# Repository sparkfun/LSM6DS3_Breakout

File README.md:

SparkFun <PRODUCT NAME>
========================================

[*LSM6DS3 Breakout (SEN-13339)*](https://www.sparkfun.com/products/13339)

The LSM6DS3 Breakout board allows easy connection to the LSM6DS3.

The LSM6DS3 is a accelerometer, gyroscope, and temperature sensor with embedded functions targeted at cellphones.  It can do high sample rates and includes an 8kB FIFO buffer for burst reads.

Repository Contents
-------------------

* **/Documentation** - Data sheets, additional product information
* **/Hardware** - Eagle design files (.brd, .sch)
* **/Libraries** - Libraries for use with the LSM6DS3 Breakout
* **/Production** - Production panel files (.brd)

Documentation
--------------
* **[Library](https://github.com/sparkfun/SparkFun_LSM6DS3_Arduino_Library)** - C++ library for the LSM6DS3 Breakout.
* **[Hookup Guide](https://learn.sparkfun.com/tutorials/lsm6ds3-breakout-hookup-guide)** - Basic hookup guide for the LSM6DS3 Breakout.

Product Versions
----------------
* [SEN-13339](https://www.sparkfun.com/products/13339)- LSM6DS3 Breakout board

Version History
---------------
* [V_1.0.0](https://github.com/sparkfun/LSM6DS3_Breakout/releases/tag/V_1.0.0) - Initial product release repository
* [V_0.3.0](https://github.com/sparkfun/LSM6DS3_Breakout/releases/tag/V_0.3.0) - HW version 0.3 release

License Information
-------------------

This product is _**open source**_! 

Please review the LICENSE.md file for license information. 

If you have any questions or concerns on licensing, please contact techsupport@sparkfun.com.

Distributed as-is; no warranty is given.

- Your friends at SparkFun.

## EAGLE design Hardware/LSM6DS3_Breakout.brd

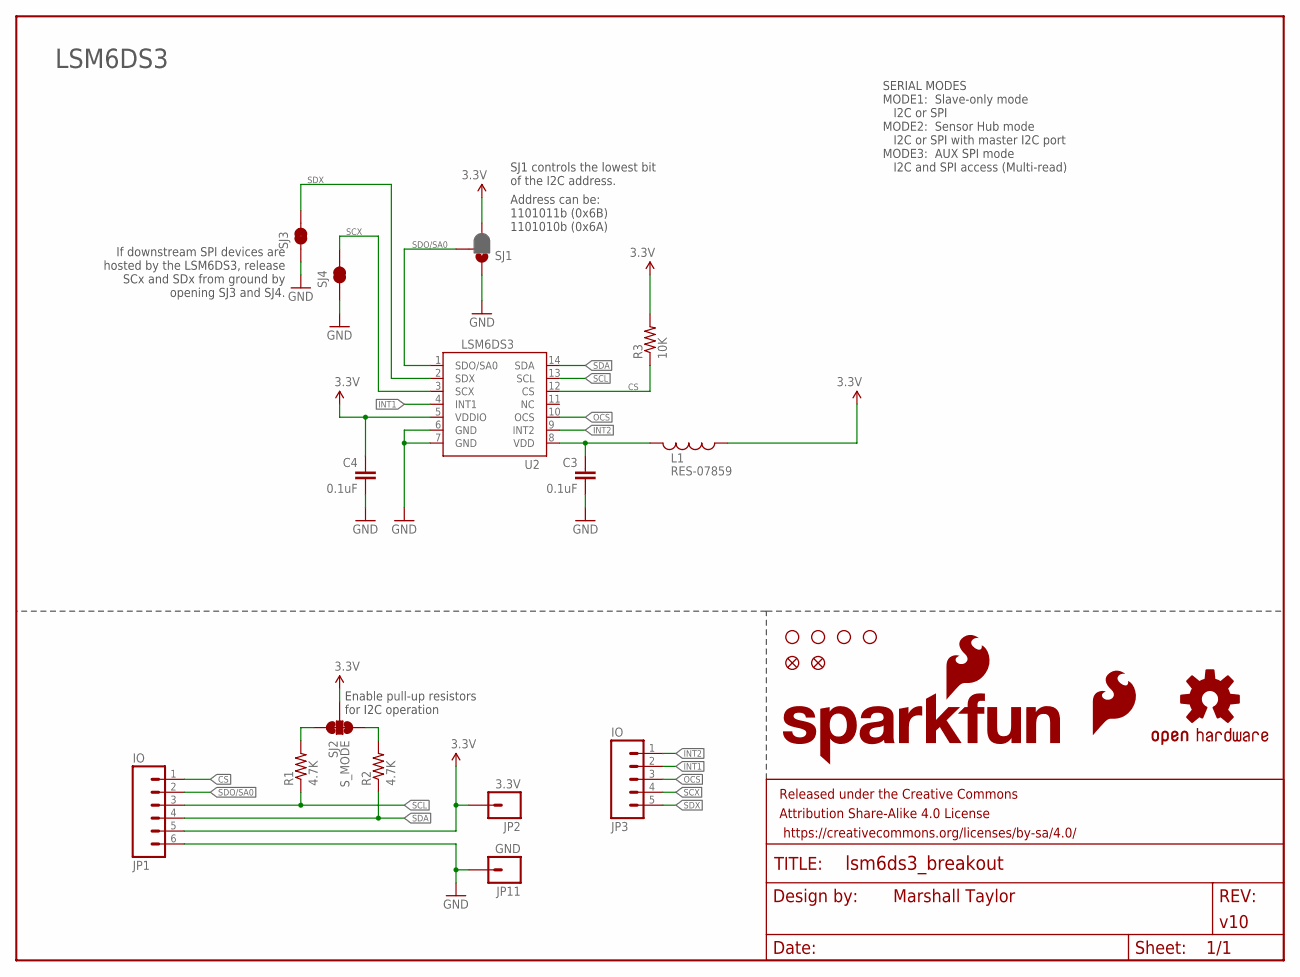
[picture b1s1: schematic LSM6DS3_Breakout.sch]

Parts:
C3, C4: 0.1uF; 0603-CAP
FID1, FID2: FIDUCIAL1X2; FIDUCIAL-1X2
FRAME1: FRAME-LETTER; CREATIVE_COMMONS
JP1: IO; 1X06_NO_SILK_YES_STOP
JP2: 3.3V; 1X01_NO_SILK
JP3: IO; 1X05
JP11: GND; 1X01_NO_SILK
L1: RES-07859; 0603
LOGO1: SFE_LOGO_FLAME.2_INCH; SFE_LOGO_FLAME_.2
LOGO2: OSHW-LOGOS; OSHW-LOGO-S
LOGO3: SFE_LOGO_NAME_FLAME.1_INCH; SFE_LOGO_NAME_FLAME_.1
R1, R2: 4.7K; 0603-RES
R3: 10K; 0603-RES
SJ1: JUMPER-PAD-3-2OF3_NC_BY_PASTE; PAD-JUMPER-3-2OF3_NC_BY_PASTE_YES_SILK_FULL_BOX
SJ2: S_MODE; PAD-JUMPER-3-3OF3_NC_BY_TRACE_YES_SILK_FULL_BOX
SJ3, SJ4: JUMPER-PAD-2-NC_BY_TRACE; PAD-JUMPER-2-NC_BY_TRACE_YES_SILK
STANDOFF1, STANDOFF2, STANDOFF3, STANDOFF4: STAND-OFF
U2: LSM6DS3; LGA14L_DOT_INDICATOR

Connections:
3.3V: C4.1, JP1.5, JP2.1, L1.1, R3.2, SJ1.3, SJ2.2, U2.5 (VDDIO)
CS: JP1.1, R3.1, U2.12 (CS)
GND: C3.2, C4.2, JP1.6, JP11.1, SJ1.1, SJ3.1, SJ4.1, U2.6 (GND), U2.7 (GND)
INT1: JP3.2, U2.4 (INT1)
INT2: JP3.1, U2.9 (INT2)
unnamed: R1.2, SJ2.1
unnamed: R2.2, SJ2.3
OCS: JP3.3, U2.10 (OCS)
SCL: JP1.3, R1.1, U2.13 (SCL)
SCX: JP3.4, SJ4.2, U2.3 (SCX)
SDA: JP1.4, R2.1, U2.14 (SDA)
SDO/SA0: JP1.2, SJ1.2, U2.1 (SDO/SA0)
SDX: JP3.5, SJ3.2, U2.2 (SDX)
VDD: C3.1, L1.2, U2.8 (VDD)

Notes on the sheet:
SJ1 controls the lowest bit of the I2C address.
LSM6DS3
If downstream SPI devices are hosted by the LSM6DS3, release SCx and SDx from ground by opening SJ3 and SJ4.
Address can be: 1101011b (0x6B) 1101010b (0x6A)
Enable pull-up resistors for I2C operation
SERIAL MODES MODE1: Slave-only mode I2C or SPI MODE2: Sensor Hub mode I2C or SPI with master I2C port MODE3: AUX SPI mode I2C and SPI access (Multi-read)

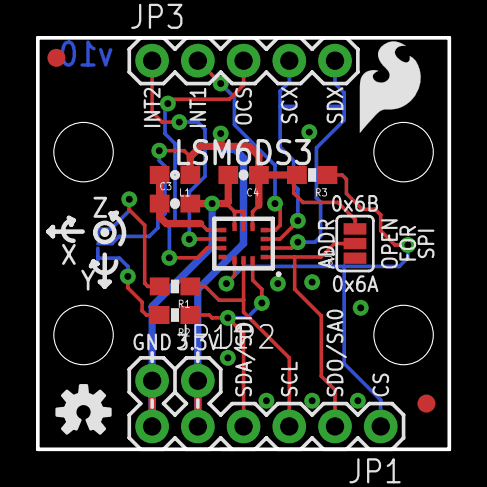
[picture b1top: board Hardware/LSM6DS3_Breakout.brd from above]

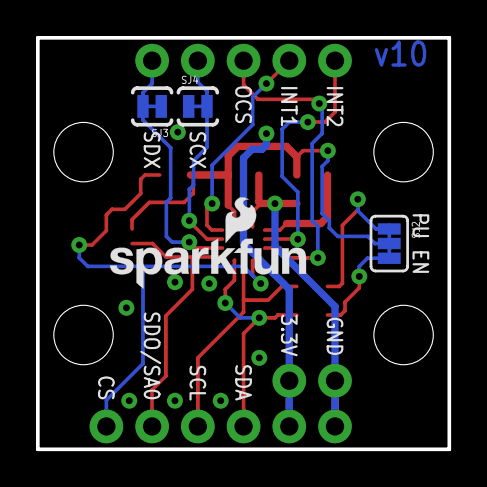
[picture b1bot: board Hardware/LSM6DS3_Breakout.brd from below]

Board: 2 copper layers, 22.9 x 22.9 mm, 25 parts (4 on the bottom side), 14 nets.

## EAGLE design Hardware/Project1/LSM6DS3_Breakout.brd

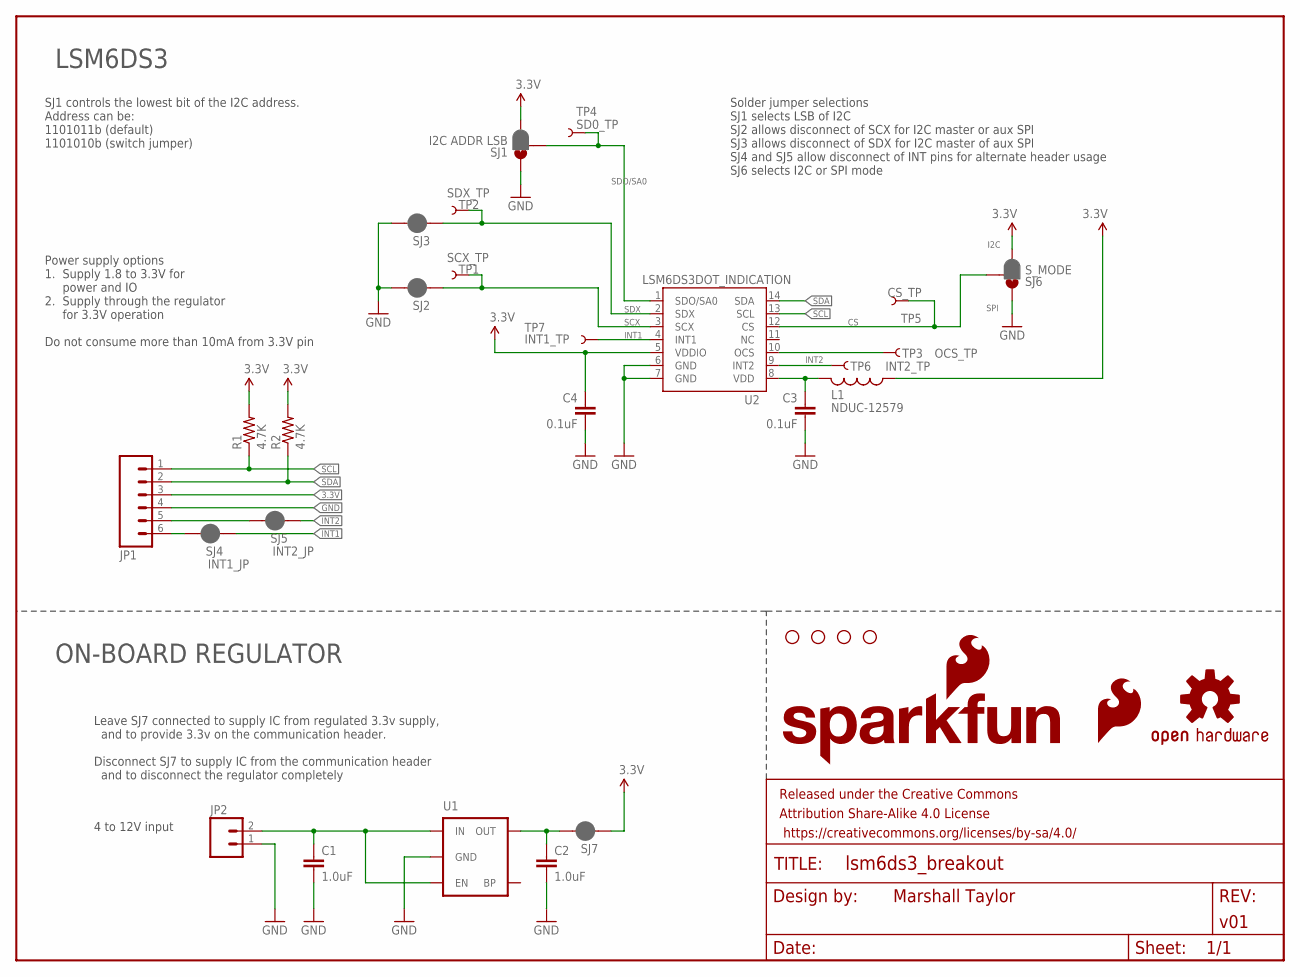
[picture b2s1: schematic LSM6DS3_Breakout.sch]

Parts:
C1, C2: 1.0uF; 0603-CAP
C3, C4: 0.1uF; 0603-CAP
FRAME1: FRAME-LETTER; CREATIVE_COMMONS
JP1: M06SILK_FEMALE_PTH; 1X06
JP2: M02PTH; 1X02
L1: NDUC-12579; 0603
LOGO1: SFE_LOGO_NAME_FLAME.1_INCH; SFE_LOGO_NAME_FLAME_.1
LOGO2: OSHW-LOGOS; OSHW-LOGO-S
LOGO3: SFE_LOGO_FLAME.4_INCH; SFE_LOGO_FLAME_.4
R1, R2: 4.7K; 0603-RES
SJ1: I2C ADDR LSB; PAD-JUMPER-3-2OF3_NC_BY_PASTE_YES_SILK_FULL_BOX
SJ2, SJ3, SJ7: JUMPER-PAD-2-NC_BY_PASTE; PAD-JUMPER-2-NC_BY_PASTE_YES_SILK
SJ4: INT1_JP; PAD-JUMPER-2-NC_BY_PASTE_YES_SILK
SJ5: INT2_JP; PAD-JUMPER-2-NC_BY_PASTE_YES_SILK
SJ6: S_MODE; PAD-JUMPER-3-2OF3_NC_BY_PASTE_YES_SILK_FULL_BOX
STANDOFF1, STANDOFF2, STANDOFF3, STANDOFF4: STAND-OFF
TP1: SCX_TP; TP_15TH
TP2: SDX_TP; TP_15TH
TP3: OCS_TP; TP_15TH
TP4: SD0_TP; TP_15TH
TP5: CS_TP; TP_15TH
TP6: INT2_TP; TP_15TH
TP7: INT1_TP; TP_15TH
U1: MIC52053.3V; SOT23-5
U2: LSM6DS3DOT_INDICATION; LGA14L_DOT_INDICATOR

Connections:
3.3V: C4.1, JP1.3, L1.1, R1.2, R2.2, SJ1.3, SJ6.3, SJ7.1, U2.5 (VDDIO)
CS: SJ6.2, TP5.P$1, U2.12 (CS)
GND: C1.2, C2.2, C3.2, C4.2, JP1.4, JP2.1, SJ1.1, SJ2.2, SJ3.2, SJ6.1, U1.2 (GND), U2.6 (GND), U2.7 (GND)
INT1: SJ4.1, TP7.P$1, U2.4 (INT1)
INT2: SJ5.1, TP6.P$1, U2.9 (INT2)
unnamed: C3.1, L1.2, U2.8 (VDD)
unnamed: TP3.P$1, U2.10 (OCS)
unnamed: JP1.5, SJ5.2
unnamed: JP1.6, SJ4.2
unnamed: C1.1, JP2.2, U1.1 (IN), U1.3 (EN)
unnamed: C2.1, SJ7.2, U1.5 (OUT)
SCL: JP1.1, R1.1, U2.13 (SCL)
SCX: SJ2.1, TP1.P$1, U2.3 (SCX)
SDA: JP1.2, R2.1, U2.14 (SDA)
SDO/SA0: SJ1.2, TP4.P$1, U2.1 (SDO/SA0)
SDX: SJ3.1, TP2.P$1, U2.2 (SDX)

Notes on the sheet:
SPI
I2C
SJ1 controls the lowest bit of the I2C address. Address can be: 1101011b (default) 1101010b (switch jumper)
Leave SJ7 connected to supply IC from regulated 3.3v supply, and to provide 3.3v on the communication header. Disconnect SJ7 to supply IC from the communication header and to disconnect the regulator completely
4 to 12V input
Do not consume more than 10mA from 3.3V pin
Power supply options 1. Supply 1.8 to 3.3V for power and IO 2. Supply through the regulator for 3.3V operation
ON-BOARD REGULATOR
LSM6DS3
Solder jumper selections SJ1 selects LSB of I2C SJ2 allows disconnect of SCX for I2C master or aux SPI SJ3 allows disconnect of SDX for I2C master of aux SPI SJ4 and SJ5 allow disconnect of INT pins for alternate header usage SJ6 selects I2C or SPI mode

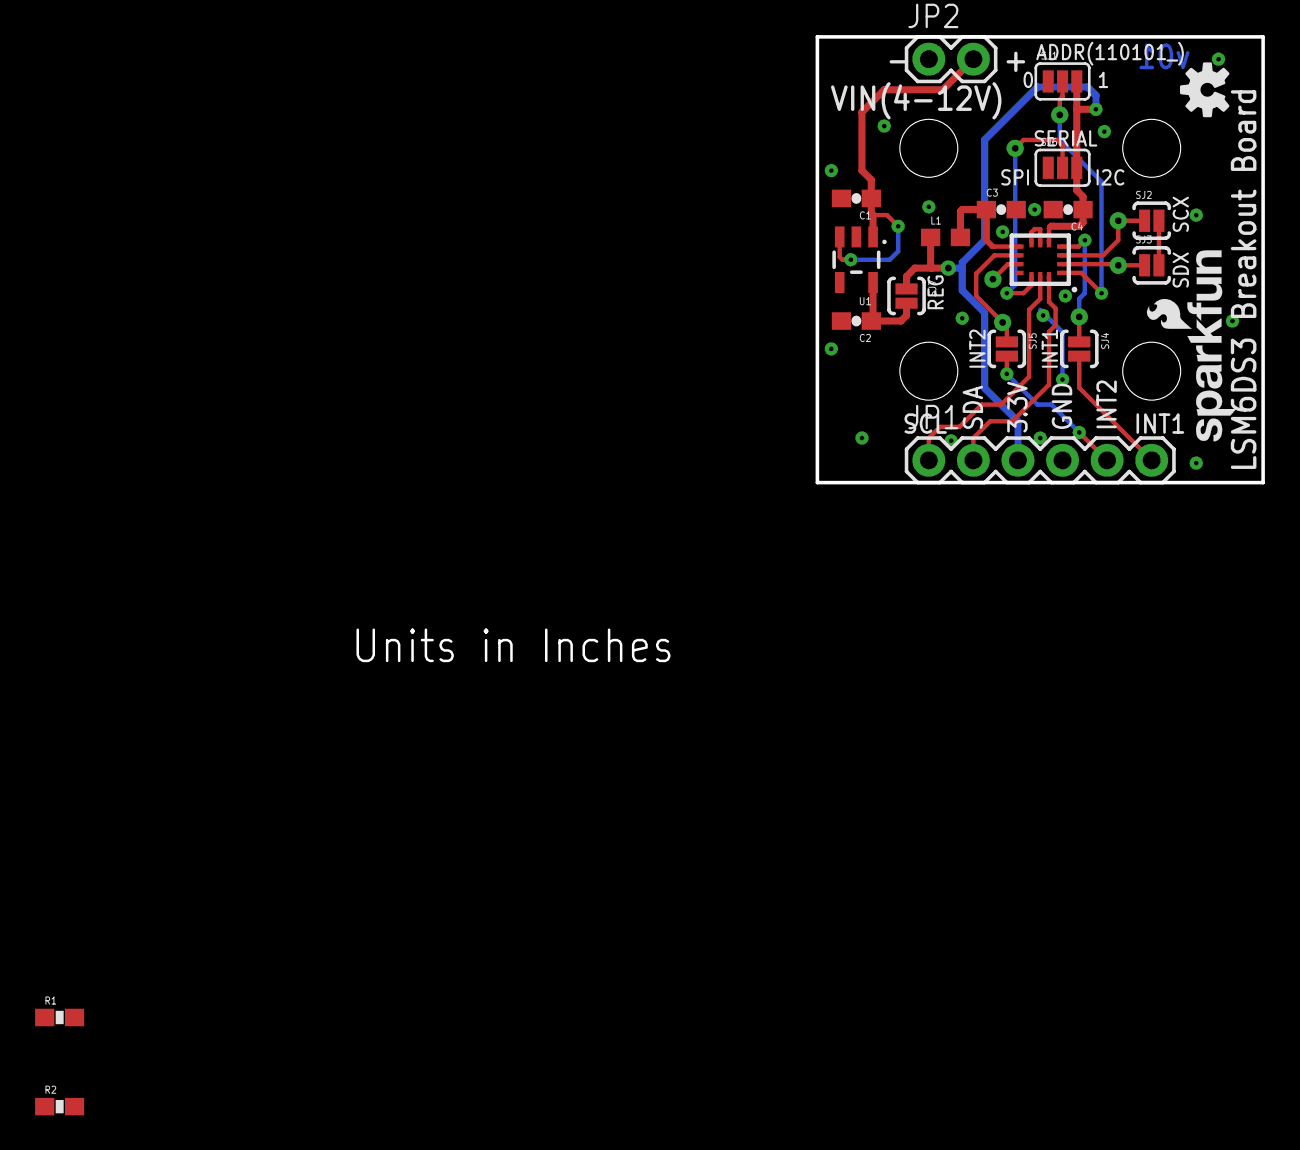
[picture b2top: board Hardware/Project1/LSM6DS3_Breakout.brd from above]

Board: 2 copper layers, 25.4 x 25.4 mm, 33 parts (1 on the bottom side), 16 nets.

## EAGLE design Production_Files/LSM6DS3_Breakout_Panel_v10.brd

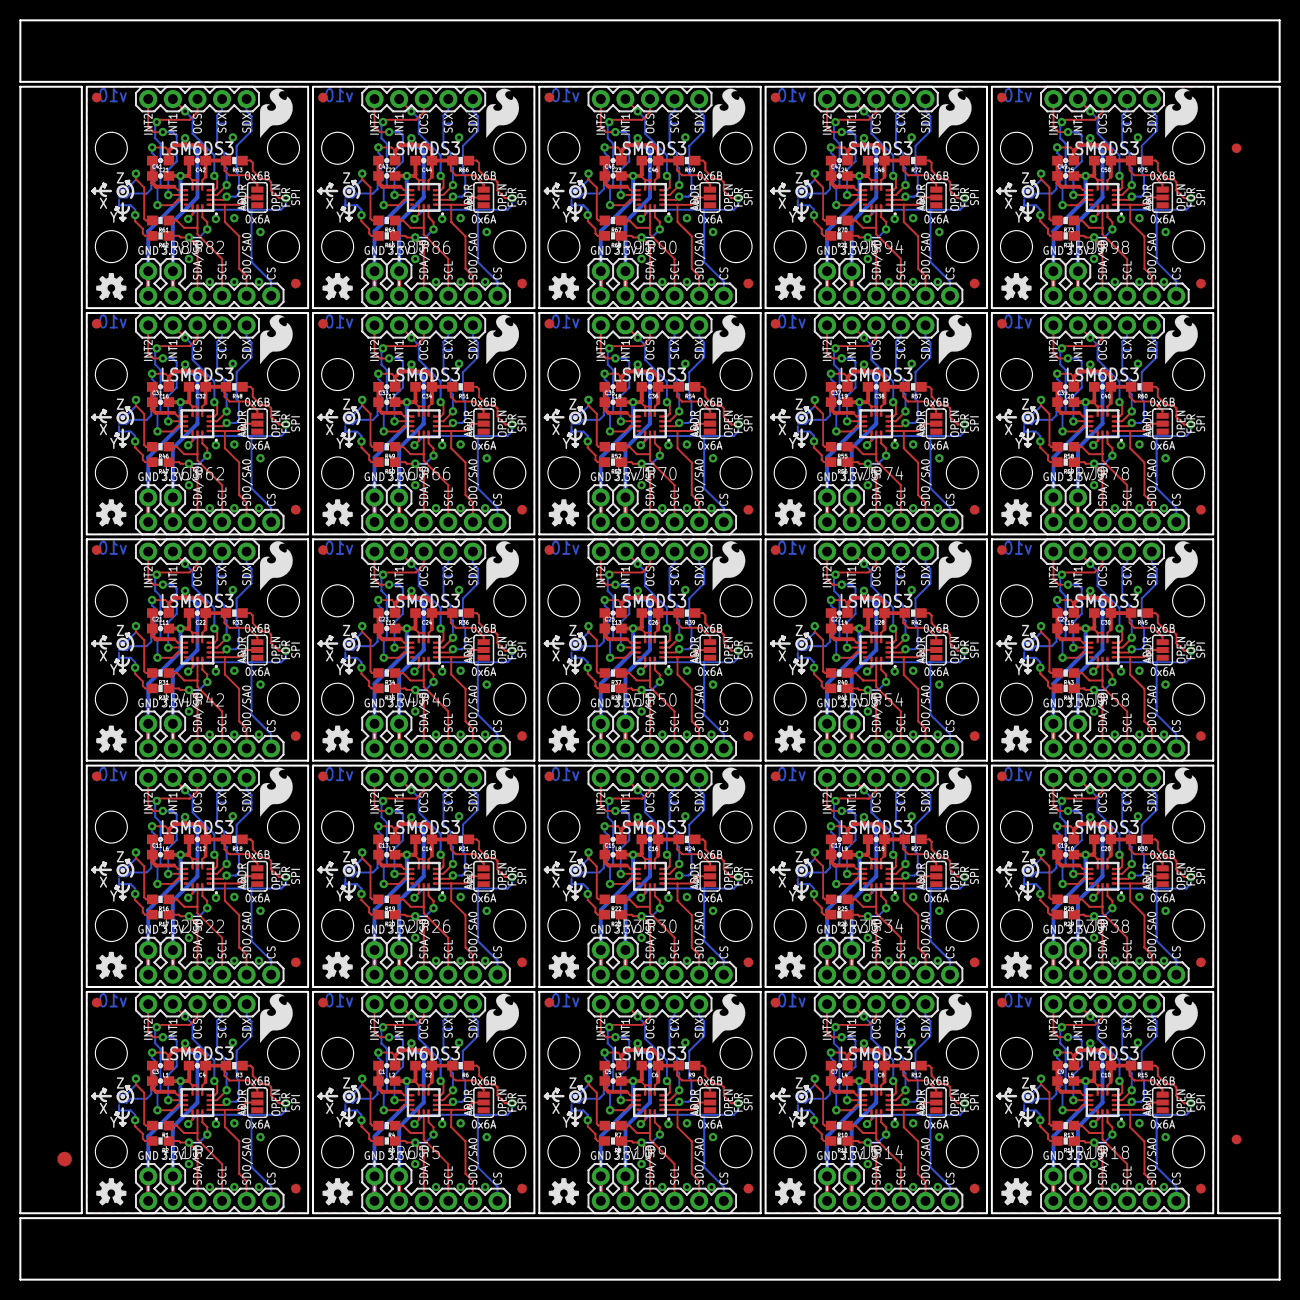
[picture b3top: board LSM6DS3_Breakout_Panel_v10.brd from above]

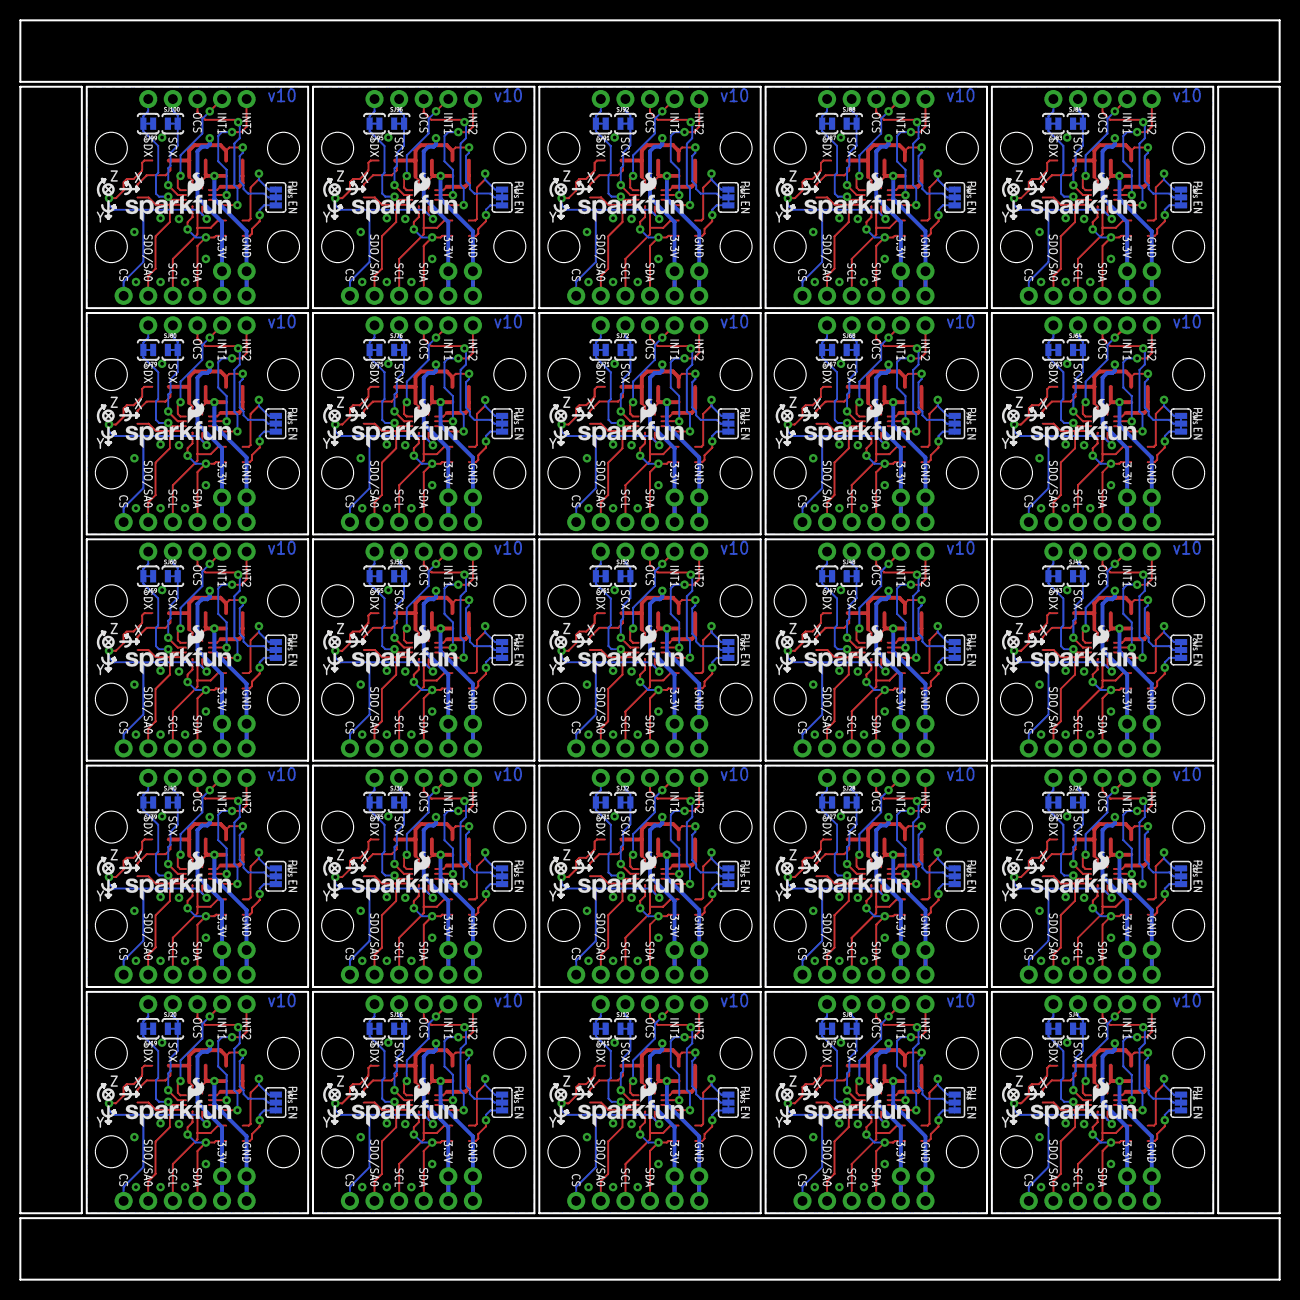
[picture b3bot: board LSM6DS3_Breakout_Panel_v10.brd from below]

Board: 2 copper layers, 130.0 x 130.0 mm, 603 parts (100 on the bottom side), 350 nets.

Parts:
C1, C2, C3, C4, C5, C6, C7, C8, C9, C10, C11, C12, C13, C14, C15, C16, C17, C18, C19, C20, C21, C22, C23, C24, C25, C26, C27, C28, C29, C30, C31, C32, C33, C34, C35, C36, C37, C38, C39, C40, C41, C42, C43, C44, C45, C46, C47, C48, C49, C50: 0.1uF; 0603-CAP
E$1: FIDUCIAL-1.5X3
E$6, E$7: FIDUCIAL-1X2
FID1, FID2, FID3, FID4, FID5, FID6, FID7, FID8, FID9, FID10, FID11, FID12, FID13, FID14, FID15, FID16, FID17, FID18, FID19, FID20, FID21, FID22, FID23, FID24, FID25, FID26, FID27, FID28, FID29, FID30, FID31, FID32, FID33, FID34, FID35, FID36, FID37, FID38, FID39, FID40, FID41, FID42, FID43, FID44, FID45, FID46, FID47, FID48, FID49, FID50: FIDUCIAL1X2; FIDUCIAL-1X2
JP1, JP4, JP8, JP13, JP17, JP21, JP25, JP29, JP33, JP37, JP41, JP45, JP49, JP53, JP57, JP61, JP65, JP69, JP73, JP77, JP81, JP85, JP89, JP93, JP97: IO; 1X06_NO_SILK_YES_STOP
JP2, JP5, JP9, JP14, JP18, JP22, JP26, JP30, JP34, JP38, JP42, JP46, JP50, JP54, JP58, JP62, JP66, JP70, JP74, JP78, JP82, JP86, JP90, JP94, JP98: 3.3V; 1X01_NO_SILK
JP3, JP7, JP12, JP16, JP20, JP24, JP28, JP32, JP36, JP40, JP44, JP48, JP52, JP56, JP60, JP64, JP68, JP72, JP76, JP80, JP84, JP88, JP92, JP96, JP100: IO; 1X05
JP6, JP10, JP11, JP15, JP19, JP23, JP27, JP31, JP35, JP39, JP43, JP47, JP51, JP55, JP59, JP63, JP67, JP71, JP75, JP79, JP83, JP87, JP91, JP95, JP99: GND; 1X01_NO_SILK
L1, L2, L3, L4, L5, L6, L7, L8, L9, L10, L11, L12, L13, L14, L15, L16, L17, L18, L19, L20, L21, L22, L23, L24, L25: RES-07859; 0603
LOGO1, LOGO4, LOGO7, LOGO10, LOGO13, LOGO16, LOGO19, LOGO22, LOGO25, LOGO28, LOGO31, LOGO34, LOGO37, LOGO40, LOGO43, LOGO46, LOGO49, LOGO52, LOGO55, LOGO58, LOGO61, LOGO64, LOGO67, LOGO70, LOGO73: SFE_LOGO_FLAME.2_INCH; SFE_LOGO_FLAME_.2
LOGO2, LOGO5, LOGO8, LOGO11, LOGO14, LOGO17, LOGO20, LOGO23, LOGO26, LOGO29, LOGO32, LOGO35, LOGO38, LOGO41, LOGO44, LOGO47, LOGO50, LOGO53, LOGO56, LOGO59, LOGO62, LOGO65, LOGO68, LOGO71, LOGO74: OSHW-LOGOS; OSHW-LOGO-S
LOGO3, LOGO6, LOGO9, LOGO12, LOGO15, LOGO18, LOGO21, LOGO24, LOGO27, LOGO30, LOGO33, LOGO36, LOGO39, LOGO42, LOGO45, LOGO48, LOGO51, LOGO54, LOGO57, LOGO60, LOGO63, LOGO66, LOGO69, LOGO72, LOGO75: SFE_LOGO_NAME_FLAME.1_INCH; SFE_LOGO_NAME_FLAME_.1
R1, R2, R4, R5, R7, R8, R10, R11, R13, R14, R16, R17, R19, R20, R22, R23, R25, R26, R28, R29, R31, R32, R34, R35, R37, R38, R40, R41, R43, R44, R46, R47, R49, R50, R52, R53, R55, R56, R58, R59, R61, R62, R64, R65, R67, R68, R70, R71, R73, R74: 4.7K; 0603-RES
R3, R6, R9, R12, R15, R18, R21, R24, R27, R30, R33, R36, R39, R42, R45, R48, R51, R54, R57, R60, R63, R66, R69, R72, R75: 10K; 0603-RES
SJ1, SJ5, SJ9, SJ13, SJ17, SJ21, SJ25, SJ29, SJ33, SJ37, SJ41, SJ45, SJ49, SJ53, SJ57, SJ61, SJ65, SJ69, SJ73, SJ77, SJ81, SJ85, SJ89, SJ93, SJ97: PAD-JUMPER-3-2OF3_NC_BY_PASTE_YES_SILK_FULL_BOX
SJ2, SJ6, SJ10, SJ14, SJ18, SJ22, SJ26, SJ30, SJ34, SJ38, SJ42, SJ46, SJ50, SJ54, SJ58, SJ62, SJ66, SJ70, SJ74, SJ78, SJ82, SJ86, SJ90, SJ94, SJ98: S_MODE; PAD-JUMPER-3-3OF3_NC_BY_TRACE_YES_SILK_FULL_BOX
SJ3, SJ4, SJ7, SJ8, SJ11, SJ12, SJ15, SJ16, SJ19, SJ20, SJ23, SJ24, SJ27, SJ28, SJ31, SJ32, SJ35, SJ36, SJ39, SJ40, SJ43, SJ44, SJ47, SJ48, SJ51, SJ52, SJ55, SJ56, SJ59, SJ60, SJ63, SJ64, SJ67, SJ68, SJ71, SJ72, SJ75, SJ76, SJ79, SJ80, SJ83, SJ84, SJ87, SJ88, SJ91, SJ92, SJ95, SJ96, SJ99, SJ100: JUMPER-PAD-2-NC_BY_TRACE; PAD-JUMPER-2-NC_BY_TRACE_YES_SILK
STANDOFF1, STANDOFF2, STANDOFF3, STANDOFF4, STANDOFF5, STANDOFF6, STANDOFF7, STANDOFF8, STANDOFF9, STANDOFF10, STANDOFF11, STANDOFF12, STANDOFF13, STANDOFF14, STANDOFF15, STANDOFF16, STANDOFF17, STANDOFF18, STANDOFF19, STANDOFF20, STANDOFF21, STANDOFF22, STANDOFF23, STANDOFF24, STANDOFF25, STANDOFF26, STANDOFF27, STANDOFF28, STANDOFF29, STANDOFF30, STANDOFF31, STANDOFF32, STANDOFF33, STANDOFF34, STANDOFF35, STANDOFF36, STANDOFF37, STANDOFF38, STANDOFF39, STANDOFF40, STANDOFF41, STANDOFF42, STANDOFF43, STANDOFF44, STANDOFF45, STANDOFF46, STANDOFF47, STANDOFF48, STANDOFF49, STANDOFF50, STANDOFF51, STANDOFF52, STANDOFF53, STANDOFF54, STANDOFF55, STANDOFF56, STANDOFF57, STANDOFF58, STANDOFF59, STANDOFF60, STANDOFF61, STANDOFF62, STANDOFF63, STANDOFF64, STANDOFF65, STANDOFF66, STANDOFF67, STANDOFF68, STANDOFF69, STANDOFF70, STANDOFF71, STANDOFF72, STANDOFF73, STANDOFF74, STANDOFF75, STANDOFF76, STANDOFF77, STANDOFF78, STANDOFF79, STANDOFF80, STANDOFF81, STANDOFF82, STANDOFF83, STANDOFF84, STANDOFF85, STANDOFF86, STANDOFF87, STANDOFF88, STANDOFF89, STANDOFF90, STANDOFF91, STANDOFF92, STANDOFF93, STANDOFF94, STANDOFF95, STANDOFF96, STANDOFF97, STANDOFF98, STANDOFF99, STANDOFF100: STAND-OFF
U1, U2, U3, U4, U5, U6, U7, U8, U9, U10, U11, U12, U13, U14, U15, U16, U17, U18, U19, U20, U21, U22, U23, U24, U25: LSM6DS3; LGA14L_DOT_INDICATOR

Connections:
3.3V: C4.1, JP1.5, JP2.1, L1.1, R3.2, SJ1.3, SJ2.2, U2.5
3.3V1: C2.1, JP4.5, JP5.1, L2.1, R6.2, SJ5.3, SJ6.2, U1.5
3.3V2: C6.1, JP8.5, JP9.1, L3.1, R9.2, SJ9.3, SJ10.2, U3.5
3.3V3: C8.1, JP13.5, JP14.1, L4.1, R12.2, SJ13.3, SJ14.2, U4.5
3.3V4: C10.1, JP17.5, JP18.1, L5.1, R15.2, SJ17.3, SJ18.2, U5.5
3.3V5: C12.1, JP21.5, JP22.1, L6.1, R18.2, SJ21.3, SJ22.2, U6.5
3.3V6: C14.1, JP25.5, JP26.1, L7.1, R21.2, SJ25.3, SJ26.2, U7.5
3.3V7: C16.1, JP29.5, JP30.1, L8.1, R24.2, SJ29.3, SJ30.2, U8.5
3.3V8: C18.1, JP33.5, JP34.1, L9.1, R27.2, SJ33.3, SJ34.2, U9.5
3.3V9: C20.1, JP37.5, JP38.1, L10.1, R30.2, SJ37.3, SJ38.2, U10.5
3.3V10: C22.1, JP41.5, JP42.1, L11.1, R33.2, SJ41.3, SJ42.2, U11.5
3.3V11: C24.1, JP45.5, JP46.1, L12.1, R36.2, SJ45.3, SJ46.2, U12.5
3.3V12: C26.1, JP49.5, JP50.1, L13.1, R39.2, SJ49.3, SJ50.2, U13.5
3.3V13: C28.1, JP53.5, JP54.1, L14.1, R42.2, SJ53.3, SJ54.2, U14.5
3.3V14: C30.1, JP57.5, JP58.1, L15.1, R45.2, SJ57.3, SJ58.2, U15.5
3.3V15: C32.1, JP61.5, JP62.1, L16.1, R48.2, SJ61.3, SJ62.2, U16.5
3.3V16: C34.1, JP65.5, JP66.1, L17.1, R51.2, SJ65.3, SJ66.2, U17.5
3.3V17: C36.1, JP69.5, JP70.1, L18.1, R54.2, SJ69.3, SJ70.2, U18.5
3.3V18: C38.1, JP73.5, JP74.1, L19.1, R57.2, SJ73.3, SJ74.2, U19.5
3.3V19: C40.1, JP77.5, JP78.1, L20.1, R60.2, SJ77.3, SJ78.2, U20.5
3.3V20: C42.1, JP81.5, JP82.1, L21.1, R63.2, SJ81.3, SJ82.2, U21.5
3.3V21: C44.1, JP85.5, JP86.1, L22.1, R66.2, SJ85.3, SJ86.2, U22.5
3.3V22: C46.1, JP89.5, JP90.1, L23.1, R69.2, SJ89.3, SJ90.2, U23.5
3.3V23: C48.1, JP93.5, JP94.1, L24.1, R72.2, SJ93.3, SJ94.2, U24.5
3.3V24: C50.1, JP97.5, JP98.1, L25.1, R75.2, SJ97.3, SJ98.2, U25.5
CS: JP1.1, R3.1, U2.12
CS1: JP4.1, R6.1, U1.12
CS2: JP8.1, R9.1, U3.12
CS3: JP13.1, R12.1, U4.12
CS4: JP17.1, R15.1, U5.12
CS5: JP21.1, R18.1, U6.12
CS6: JP25.1, R21.1, U7.12
CS7: JP29.1, R24.1, U8.12
CS8: JP33.1, R27.1, U9.12
CS9: JP37.1, R30.1, U10.12
CS10: JP41.1, R33.1, U11.12
CS11: JP45.1, R36.1, U12.12
CS12: JP49.1, R39.1, U13.12
CS13: JP53.1, R42.1, U14.12
CS14: JP57.1, R45.1, U15.12
CS15: JP61.1, R48.1, U16.12
CS16: JP65.1, R51.1, U17.12
CS17: JP69.1, R54.1, U18.12
CS18: JP73.1, R57.1, U19.12
CS19: JP77.1, R60.1, U20.12
CS20: JP81.1, R63.1, U21.12
CS21: JP85.1, R66.1, U22.12
CS22: JP89.1, R69.1, U23.12
CS23: JP93.1, R72.1, U24.12
CS24: JP97.1, R75.1, U25.12
GND: C3.2, C4.2, JP1.6, JP11.1, SJ1.1, SJ3.1, SJ4.1, U2.6, U2.7
GND1: C1.2, C2.2, JP4.6, JP6.1, SJ5.1, SJ7.1, SJ8.1, U1.6, U1.7
GND2: C5.2, C6.2, JP8.6, JP10.1, SJ9.1, SJ11.1, SJ12.1, U3.6, U3.7
GND3: C7.2, C8.2, JP13.6, JP15.1, SJ13.1, SJ15.1, SJ16.1, U4.6, U4.7
GND4: C9.2, C10.2, JP17.6, JP19.1, SJ17.1, SJ19.1, SJ20.1, U5.6, U5.7
GND5: C11.2, C12.2, JP21.6, JP23.1, SJ21.1, SJ23.1, SJ24.1, U6.6, U6.7
GND6: C13.2, C14.2, JP25.6, JP27.1, SJ25.1, SJ27.1, SJ28.1, U7.6, U7.7
GND7: C15.2, C16.2, JP29.6, JP31.1, SJ29.1, SJ31.1, SJ32.1, U8.6, U8.7
GND8: C17.2, C18.2, JP33.6, JP35.1, SJ33.1, SJ35.1, SJ36.1, U9.6, U9.7
GND9: C19.2, C20.2, JP37.6, JP39.1, SJ37.1, SJ39.1, SJ40.1, U10.6, U10.7
GND10: C21.2, C22.2, JP41.6, JP43.1, SJ41.1, SJ43.1, SJ44.1, U11.6, U11.7
GND11: C23.2, C24.2, JP45.6, JP47.1, SJ45.1, SJ47.1, SJ48.1, U12.6, U12.7
GND12: C25.2, C26.2, JP49.6, JP51.1, SJ49.1, SJ51.1, SJ52.1, U13.6, U13.7
GND13: C27.2, C28.2, JP53.6, JP55.1, SJ53.1, SJ55.1, SJ56.1, U14.6, U14.7
GND14: C29.2, C30.2, JP57.6, JP59.1, SJ57.1, SJ59.1, SJ60.1, U15.6, U15.7
GND15: C31.2, C32.2, JP61.6, JP63.1, SJ61.1, SJ63.1, SJ64.1, U16.6, U16.7
GND16: C33.2, C34.2, JP65.6, JP67.1, SJ65.1, SJ67.1, SJ68.1, U17.6, U17.7
GND17: C35.2, C36.2, JP69.6, JP71.1, SJ69.1, SJ71.1, SJ72.1, U18.6, U18.7
GND18: C37.2, C38.2, JP73.6, JP75.1, SJ73.1, SJ75.1, SJ76.1, U19.6, U19.7
GND19: C39.2, C40.2, JP77.6, JP79.1, SJ77.1, SJ79.1, SJ80.1, U20.6, U20.7
GND20: C41.2, C42.2, JP81.6, JP83.1, SJ81.1, SJ83.1, SJ84.1, U21.6, U21.7
GND21: C43.2, C44.2, JP85.6, JP87.1, SJ85.1, SJ87.1, SJ88.1, U22.6, U22.7
GND22: C45.2, C46.2, JP89.6, JP91.1, SJ89.1, SJ91.1, SJ92.1, U23.6, U23.7
GND23: C47.2, C48.2, JP93.6, JP95.1, SJ93.1, SJ95.1, SJ96.1, U24.6, U24.7
GND24: C49.2, C50.2, JP97.6, JP99.1, SJ97.1, SJ99.1, SJ100.1, U25.6, U25.7
INT1: JP3.2, U2.4
INT2: JP3.1, U2.9
INT3: JP7.2, U1.4
INT4: JP7.1, U1.9
INT5: JP12.2, U3.4
INT6: JP12.1, U3.9
INT7: JP16.2, U4.4
INT8: JP16.1, U4.9
INT9: JP20.2, U5.4
INT10: JP20.1, U5.9
INT11: JP24.2, U6.4
INT12: JP24.1, U6.9
INT13: JP28.2, U7.4
INT14: JP28.1, U7.9
INT15: JP32.2, U8.4
INT16: JP32.1, U8.9
INT17: JP36.2, U9.4
INT18: JP36.1, U9.9
INT19: JP40.2, U10.4
INT20: JP40.1, U10.9
INT21: JP44.2, U11.4
INT22: JP44.1, U11.9
INT23: JP48.2, U12.4
INT24: JP48.1, U12.9
INT25: JP52.2, U13.4
INT26: JP52.1, U13.9
INT27: JP56.2, U14.4
INT28: JP56.1, U14.9
INT29: JP60.2, U15.4
INT30: JP60.1, U15.9
INT31: JP64.2, U16.4
INT32: JP64.1, U16.9
INT33: JP68.2, U17.4
INT34: JP68.1, U17.9
INT35: JP72.2, U18.4
INT36: JP72.1, U18.9
INT37: JP76.2, U19.4
INT38: JP76.1, U19.9
INT39: JP80.2, U20.4
INT40: JP80.1, U20.9
INT41: JP84.2, U21.4
INT42: JP84.1, U21.9
INT43: JP88.2, U22.4
INT44: JP88.1, U22.9
INT45: JP92.2, U23.4
INT46: JP92.1, U23.9
INT47: JP96.2, U24.4
INT48: JP96.1, U24.9
INT49: JP100.2, U25.4
INT50: JP100.1, U25.9
unnamed: R4.2, SJ6.1
unnamed: R5.2, SJ6.3
unnamed: R7.2, SJ10.1
unnamed: R8.2, SJ10.3
unnamed: R1.2, SJ2.1
unnamed: R2.2, SJ2.3
unnamed: R10.2, SJ14.1
unnamed: R11.2, SJ14.3
unnamed: R13.2, SJ18.1
unnamed: R14.2, SJ18.3
unnamed: R16.2, SJ22.1
unnamed: R17.2, SJ22.3
unnamed: R19.2, SJ26.1
unnamed: R20.2, SJ26.3
unnamed: R22.2, SJ30.1
unnamed: R23.2, SJ30.3
unnamed: R25.2, SJ34.1
unnamed: R26.2, SJ34.3
unnamed: R28.2, SJ38.1
unnamed: R29.2, SJ38.3
unnamed: R31.2, SJ42.1
unnamed: R32.2, SJ42.3
unnamed: R34.2, SJ46.1
unnamed: R35.2, SJ46.3
unnamed: R37.2, SJ50.1
unnamed: R38.2, SJ50.3
unnamed: R40.2, SJ54.1
unnamed: R41.2, SJ54.3
unnamed: R43.2, SJ58.1
unnamed: R44.2, SJ58.3
unnamed: R46.2, SJ62.1
unnamed: R47.2, SJ62.3
unnamed: R49.2, SJ66.1
unnamed: R50.2, SJ66.3
unnamed: R52.2, SJ70.1
unnamed: R53.2, SJ70.3
unnamed: R55.2, SJ74.1
unnamed: R56.2, SJ74.3
unnamed: R58.2, SJ78.1
unnamed: R59.2, SJ78.3
unnamed: R61.2, SJ82.1
unnamed: R62.2, SJ82.3
unnamed: R64.2, SJ86.1
unnamed: R65.2, SJ86.3
unnamed: R67.2, SJ90.1
unnamed: R68.2, SJ90.3
unnamed: R70.2, SJ94.1
unnamed: R71.2, SJ94.3
unnamed: R73.2, SJ98.1
unnamed: R74.2, SJ98.3
OCS: JP3.3, U2.10
OCS1: JP7.3, U1.10
OCS2: JP12.3, U3.10
OCS3: JP16.3, U4.10
OCS4: JP20.3, U5.10
OCS5: JP24.3, U6.10
OCS6: JP28.3, U7.10
OCS7: JP32.3, U8.10
OCS8: JP36.3, U9.10
OCS9: JP40.3, U10.10
OCS10: JP44.3, U11.10
OCS11: JP48.3, U12.10
OCS12: JP52.3, U13.10
OCS13: JP56.3, U14.10
OCS14: JP60.3, U15.10
OCS15: JP64.3, U16.10
OCS16: JP68.3, U17.10
OCS17: JP72.3, U18.10
OCS18: JP76.3, U19.10
OCS19: JP80.3, U20.10
OCS20: JP84.3, U21.10
OCS21: JP88.3, U22.10
OCS22: JP92.3, U23.10
OCS23: JP96.3, U24.10
OCS24: JP100.3, U25.10
SCL: JP1.3, R1.1, U2.13
SCL1: JP4.3, R4.1, U1.13
SCL2: JP8.3, R7.1, U3.13
SCL3: JP13.3, R10.1, U4.13
SCL4: JP17.3, R13.1, U5.13
SCL5: JP21.3, R16.1, U6.13
SCL6: JP25.3, R19.1, U7.13
SCL7: JP29.3, R22.1, U8.13
SCL8: JP33.3, R25.1, U9.13
SCL9: JP37.3, R28.1, U10.13
SCL10: JP41.3, R31.1, U11.13
SCL11: JP45.3, R34.1, U12.13
SCL12: JP49.3, R37.1, U13.13
SCL13: JP53.3, R40.1, U14.13
SCL14: JP57.3, R43.1, U15.13
SCL15: JP61.3, R46.1, U16.13
SCL16: JP65.3, R49.1, U17.13
SCL17: JP69.3, R52.1, U18.13
SCL18: JP73.3, R55.1, U19.13
SCL19: JP77.3, R58.1, U20.13
SCL20: JP81.3, R61.1, U21.13
SCL21: JP85.3, R64.1, U22.13
SCL22: JP89.3, R67.1, U23.13
SCL23: JP93.3, R70.1, U24.13
SCL24: JP97.3, R73.1, U25.13
SCX: JP3.4, SJ4.2, U2.3
SCX1: JP7.4, SJ8.2, U1.3
SCX2: JP12.4, SJ12.2, U3.3
SCX3: JP16.4, SJ16.2, U4.3
SCX4: JP20.4, SJ20.2, U5.3
SCX5: JP24.4, SJ24.2, U6.3
SCX6: JP28.4, SJ28.2, U7.3
SCX7: JP32.4, SJ32.2, U8.3
SCX8: JP36.4, SJ36.2, U9.3
SCX9: JP40.4, SJ40.2, U10.3
SCX10: JP44.4, SJ44.2, U11.3
SCX11: JP48.4, SJ48.2, U12.3
SCX12: JP52.4, SJ52.2, U13.3
SCX13: JP56.4, SJ56.2, U14.3
SCX14: JP60.4, SJ60.2, U15.3
SCX15: JP64.4, SJ64.2, U16.3
SCX16: JP68.4, SJ68.2, U17.3
SCX17: JP72.4, SJ72.2, U18.3
SCX18: JP76.4, SJ76.2, U19.3
SCX19: JP80.4, SJ80.2, U20.3
SCX20: JP84.4, SJ84.2, U21.3
SCX21: JP88.4, SJ88.2, U22.3
SCX22: JP92.4, SJ92.2, U23.3
SCX23: JP96.4, SJ96.2, U24.3
SCX24: JP100.4, SJ100.2, U25.3
SDA: JP1.4, R2.1, U2.14
SDA1: JP4.4, R5.1, U1.14
SDA2: JP8.4, R8.1, U3.14
SDA3: JP13.4, R11.1, U4.14
SDA4: JP17.4, R14.1, U5.14
SDA5: JP21.4, R17.1, U6.14
SDA6: JP25.4, R20.1, U7.14
SDA7: JP29.4, R23.1, U8.14
SDA8: JP33.4, R26.1, U9.14
SDA9: JP37.4, R29.1, U10.14
SDA10: JP41.4, R32.1, U11.14
SDA11: JP45.4, R35.1, U12.14
SDA12: JP49.4, R38.1, U13.14
SDA13: JP53.4, R41.1, U14.14
SDA14: JP57.4, R44.1, U15.14
SDA15: JP61.4, R47.1, U16.14
SDA16: JP65.4, R50.1, U17.14
SDA17: JP69.4, R53.1, U18.14
SDA18: JP73.4, R56.1, U19.14
SDA19: JP77.4, R59.1, U20.14
SDA20: JP81.4, R62.1, U21.14
SDA21: JP85.4, R65.1, U22.14
SDA22: JP89.4, R68.1, U23.14
SDA23: JP93.4, R71.1, U24.14
SDA24: JP97.4, R74.1, U25.14
SDO/SA0: JP1.2, SJ1.2, U2.1
SDO/SA1: JP4.2, SJ5.2, U1.1
SDO/SA2: JP8.2, SJ9.2, U3.1
SDO/SA3: JP13.2, SJ13.2, U4.1
SDO/SA4: JP17.2, SJ17.2, U5.1
SDO/SA5: JP21.2, SJ21.2, U6.1
SDO/SA6: JP25.2, SJ25.2, U7.1
SDO/SA7: JP29.2, SJ29.2, U8.1
SDO/SA8: JP33.2, SJ33.2, U9.1
SDO/SA9: JP37.2, SJ37.2, U10.1
SDO/SA10: JP41.2, SJ41.2, U11.1
SDO/SA11: JP45.2, SJ45.2, U12.1
SDO/SA12: JP49.2, SJ49.2, U13.1
SDO/SA13: JP53.2, SJ53.2, U14.1
SDO/SA14: JP57.2, SJ57.2, U15.1
SDO/SA15: JP61.2, SJ61.2, U16.1
SDO/SA16: JP65.2, SJ65.2, U17.1
SDO/SA17: JP69.2, SJ69.2, U18.1
SDO/SA18: JP73.2, SJ73.2, U19.1
SDO/SA19: JP77.2, SJ77.2, U20.1
SDO/SA20: JP81.2, SJ81.2, U21.1
SDO/SA21: JP85.2, SJ85.2, U22.1
SDO/SA22: JP89.2, SJ89.2, U23.1
SDO/SA23: JP93.2, SJ93.2, U24.1
SDO/SA24: JP97.2, SJ97.2, U25.1
SDX: JP3.5, SJ3.2, U2.2
SDX1: JP7.5, SJ7.2, U1.2
SDX2: JP12.5, SJ11.2, U3.2
SDX3: JP16.5, SJ15.2, U4.2
SDX4: JP20.5, SJ19.2, U5.2
SDX5: JP24.5, SJ23.2, U6.2
SDX6: JP28.5, SJ27.2, U7.2
SDX7: JP32.5, SJ31.2, U8.2
SDX8: JP36.5, SJ35.2, U9.2
SDX9: JP40.5, SJ39.2, U10.2
SDX10: JP44.5, SJ43.2, U11.2
SDX11: JP48.5, SJ47.2, U12.2
SDX12: JP52.5, SJ51.2, U13.2
SDX13: JP56.5, SJ55.2, U14.2
SDX14: JP60.5, SJ59.2, U15.2
SDX15: JP64.5, SJ63.2, U16.2
SDX16: JP68.5, SJ67.2, U17.2
SDX17: JP72.5, SJ71.2, U18.2
SDX18: JP76.5, SJ75.2, U19.2
SDX19: JP80.5, SJ79.2, U20.2
SDX20: JP84.5, SJ83.2, U21.2
SDX21: JP88.5, SJ87.2, U22.2
SDX22: JP92.5, SJ91.2, U23.2
SDX23: JP96.5, SJ95.2, U24.2
SDX24: JP100.5, SJ99.2, U25.2
VDD: C3.1, L1.2, U2.8
VDD1: C1.1, L2.2, U1.8
VDD2: C5.1, L3.2, U3.8
VDD3: C7.1, L4.2, U4.8
VDD4: C9.1, L5.2, U5.8
VDD5: C11.1, L6.2, U6.8
VDD6: C13.1, L7.2, U7.8
VDD7: C15.1, L8.2, U8.8
VDD8: C17.1, L9.2, U9.8
VDD9: C19.1, L10.2, U10.8
VDD10: C21.1, L11.2, U11.8
VDD11: C23.1, L12.2, U12.8
VDD12: C25.1, L13.2, U13.8
VDD13: C27.1, L14.2, U14.8
VDD14: C29.1, L15.2, U15.8
VDD15: C31.1, L16.2, U16.8
VDD16: C33.1, L17.2, U17.8
VDD17: C35.1, L18.2, U18.8
VDD18: C37.1, L19.2, U19.8
VDD19: C39.1, L20.2, U20.8
VDD20: C41.1, L21.2, U21.8
VDD21: C43.1, L22.2, U22.8
VDD22: C45.1, L23.2, U23.8
VDD23: C47.1, L24.2, U24.8
VDD24: C49.1, L25.2, U25.8

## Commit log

2015-03-25 Initial HW commit
2015-03-25 ready for proto
2015-03-25 Removed 'template archive' files
2015-03-25 Fixed pull-ups
2015-03-26 Moved eagle project
2015-03-26 Swapped choke
2015-03-27 Fixed ripped up component
2015-03-30 Switched pads for pins, grew board.
2015-04-01 Corrected QC suggestions
2015-04-01 Fixed erroneous floating silk text
2015-04-16 Hollow I2C functions
2015-04-21 basic serial writer
2015-04-21 built arduino project
2015-04-21 added getRegion()
2015-04-21 added readTemp(), accurate
2015-04-24 SPI and I2C functional
2015-04-24 Re-organized file structure for Arduino IDE
2015-04-30 v03 commit
2015-05-01 Fixed QC Issues
2015-05-01 Taking work home
2015-06-02 Cleaning repo
2015-06-11 Fixed silk for redboards
2015-06-15 Fixed Silk
2015-06-30 created panel v10
2015-08-06 removed old files
2015-08-06 inserted new files
2015-08-06 Documentation edits
2015-08-06 Squashed 'Libraries/Arduino/' content from commit fdb8ef4
    git-subtree-dir: Libraries/Arduino
    git-subtree-split: fdb8ef44369df43f16a7f1419b3a912071b49a01
2015-08-06 fixed typo
2015-08-06 Rearticulating library imports
2015-08-06 Squashed 'Libraries/Arduino/' content from commit 79e3b6b
    git-subtree-dir: Libraries/Arduino
    git-subtree-split: 79e3b6b4ac0c7d8ae5783147f556e840cbd6f981

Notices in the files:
parts and their libraries:
SparkFun-Aesthetics: Licensing: Creative Commons ShareAlike 4.0 International - https://creativecommons.org/licenses/by-sa/4.0
SparkFun-Aesthetics: Released under the Creative Commons Attribution Share-Alike 4.0 License
SparkFun-Aesthetics: https://creativecommons.org/licenses/by-sa/4.0
